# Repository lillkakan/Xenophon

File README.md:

# Xenophon split keyboard

Xenophon is a split keyboard with a design based on the ErgoDox EZ but for less keys for the thumps and another layout for the side keys.

## Features

### Ortholinear design

The keyboard features an ortholinear design based on the ErgoDox EZ.

### 70 buttons

The keyboard features 70 buttons to replicate a standard 60% keyboard as much as possible.
The Default layout is in swedish and has all the letters and numbers.

### TRS jack connection

The PCB is designed with a trs jack nicley placed between the tilted keys.
The two processors sent data through the serial bitbang protocol.

### Smart flashing design

I did not want to include a usb port on the right PCB i added two usb pins (D+ and D-) on both sides so that i could solder all the componens except the left processors and flash the right side easily.

### USB-C

The PCB features a usb type c port with capability to connect via a usb-c to usb-c cable or a standard usb-c to usb-a cable.

### 3D printable chassi

The chassi for the keyboard is 3D printable and is designed to be as small as possible while still protecting the PCB and the electrical components.

### Relativly low cost

The total cost of the key board is around 1 300 SEK.
Which is less than similar keyboards like the ErgoDox EZ.

## Made with

Quantum Mechanical Keyboard Firmware: [qmk_firmware](https://github.com/qmk/qmk_firmware)

## Made with help from

Keyboard layout editor: [keyboard-layout-editor.com](http://www.keyboard-layout-editor.com/)

Parametric Mechanical Keycap Library: [KeyV2](https://github.com/rsheldiii/KeyV2)

Keyboard Firmware Builder: [kbfirmware.com](https://kbfirmware.com/)

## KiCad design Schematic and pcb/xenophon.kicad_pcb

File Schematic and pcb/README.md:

# Xenophon Schematic and PCB

### Schematic

Feutures a usb-c connection on the left (master) side.

Because I wanted the right PCB to have as few IO connectors as possible i made the decision to place two pin holes connected to the USB pins on the processor.
This made is so I could connect the USB pins on the left side with the ones on the right side and flash the right processor with the USB-C cable before i soldered the left processor.
The two pins can also be connected to two resistors and soldered to a USB cable to flash to the processor directly.

Small reset buttons take up unneccesary space on the pcb i added pins for for both sides reset connection designed so that a regular cable could pull the reset down.

### Components

- 70x Cherry switches
- 70x Diodes
- 1x  USB-C Receptacle
- 2x  Atmega 32u4
- 2x  16 Mhz Crystal
- 2x  3.5 TRS jack
- 5x  0.1u  Capacitor
- 4x  18p   Capacitor
- 2x  1u    Capacitor
- 1x  4.7u  Capacitor
- 4x  10k   Ohm Resistors
- 2x  22    Ohm Resistors
- 2x  5.1k  Ohm Resistors

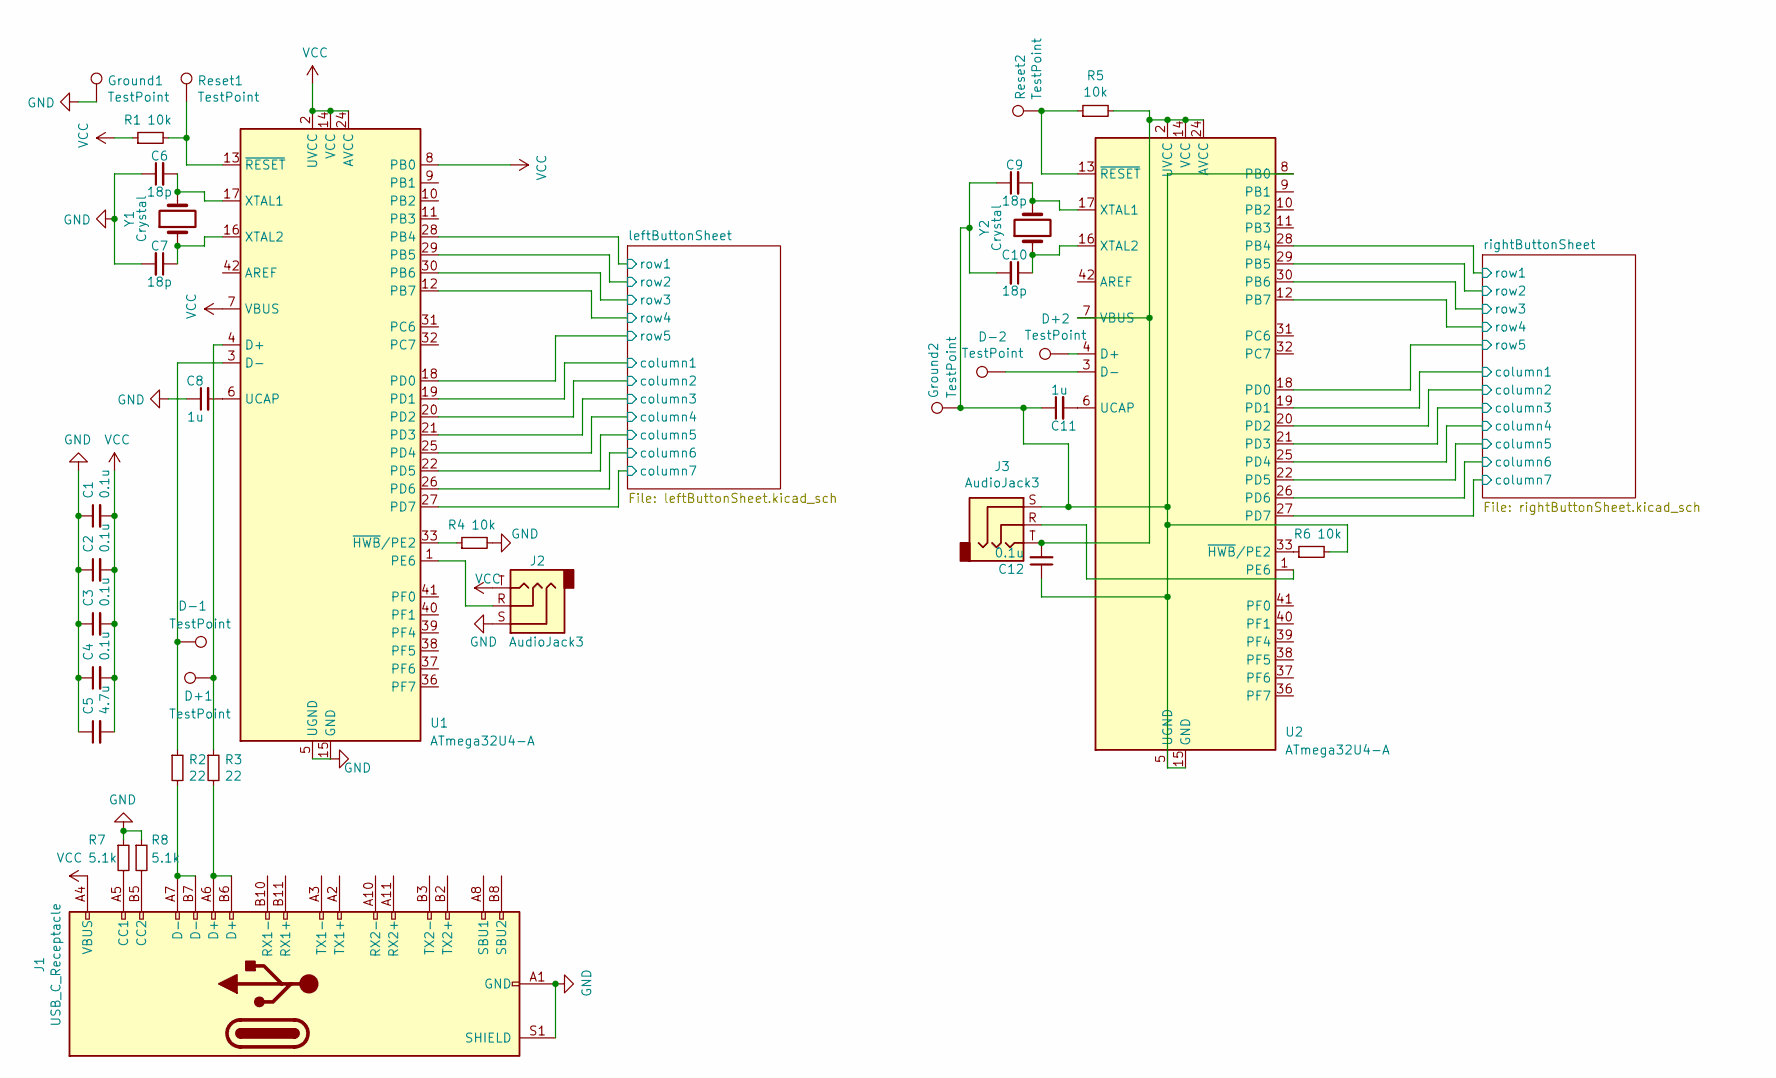
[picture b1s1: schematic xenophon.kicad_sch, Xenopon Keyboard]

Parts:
C1, C2, C3, C4, C12: 0.1u; C_1206_3216Metric
C5: 4.7u; C_1206_3216Metric
C6, C7, C9, C10: 18p; C_1206_3216Metric
C8, C11: 1u; C_1206_3216Metric
D+1, D+2: TestPoint; TestPoint_THTPad_2.0x2.0mm_Drill1.0mm
D-1, D-2: TestPoint; TestPoint_THTPad_2.0x2.0mm_Drill1.0mm
Ground1, Ground2: TestPoint; TestPoint_THTPad_2.0x2.0mm_Drill1.0mm
J1: USB_C_Receptacle; USB_C_Receptacle_HRO_TYPE-C-31-M-12
J2, J3: AudioJack3; Jack_3.5mm_Switronic_ST-005-G_horizontal
R1, R4, R5, R6: 10k; R_1206_3216Metric
R2, R3: 22; R_1206_3216Metric
R7, R8: 5.1k; R_1206_3216Metric
Reset1, Reset2: TestPoint; TestPoint_THTPad_2.0x2.0mm_Drill1.0mm
U1, U2: ATmega32U4-A; TQFP-44_10x10mm_P0.8mm
Y1, Y2: Crystal; Crystal_SMD_2016-4Pin_2.0x1.6mm

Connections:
/leftButtonSheet/column1: U1.19 (PD1); also elsewhere on the board
/leftButtonSheet/column2: U1.20 (PD2); also elsewhere on the board
/leftButtonSheet/column3: U1.21 (PD3); also elsewhere on the board
/leftButtonSheet/column4: U1.25 (PD4); also elsewhere on the board
/leftButtonSheet/column5: U1.22 (PD5); also elsewhere on the board
/leftButtonSheet/column6: U1.26 (PD6); also elsewhere on the board
/leftButtonSheet/column7: U1.27 (PD7); also elsewhere on the board
/leftButtonSheet/row1: U1.28 (PB4); also elsewhere on the board
/leftButtonSheet/row2: U1.29 (PB5); also elsewhere on the board
/leftButtonSheet/row3: U1.30 (PB6); also elsewhere on the board
/leftButtonSheet/row4: U1.12 (PB7); also elsewhere on the board
/leftButtonSheet/row5: U1.18 (PD0); also elsewhere on the board
/rightButtonSheet/column1: U2.19 (PD1); also elsewhere on the board
/rightButtonSheet/column2: U2.20 (PD2); also elsewhere on the board
/rightButtonSheet/column3: U2.21 (PD3); also elsewhere on the board
/rightButtonSheet/column4: U2.25 (PD4); also elsewhere on the board
/rightButtonSheet/column5: U2.22 (PD5); also elsewhere on the board
/rightButtonSheet/column6: U2.26 (PD6); also elsewhere on the board
/rightButtonSheet/column7: U2.27 (PD7); also elsewhere on the board
/rightButtonSheet/row1: U2.28 (PB4); also elsewhere on the board
/rightButtonSheet/row2: U2.29 (PB5); also elsewhere on the board
/rightButtonSheet/row3: U2.30 (PB6); also elsewhere on the board
/rightButtonSheet/row4: U2.12 (PB7); also elsewhere on the board
/rightButtonSheet/row5: U2.18 (PD0); also elsewhere on the board
unnamed: C7.1, U1.16 (XTAL2), Y1.1
unnamed: C8.2, U1.6 (UCAP)
unnamed: C10.1, U2.16 (XTAL2), Y2.1
unnamed: C11.2, U2.6 (UCAP)
unnamed: C12.2, J3.T, R5.2, U2.2 (UVCC), U2.7 (VBUS), U2.14 (VCC), U2.24 (AVCC), U2.34 (VCC), U2.44 (AVCC)
unnamed 99: D+1.1, R3.1, U1.4 (D+); also elsewhere on the board
unnamed 100: D+2.1, U2.4 (D+); also elsewhere on the board
unnamed 101: D-1.1, R2.1, U1.3 (D-); also elsewhere on the board
unnamed 102: D-2.1, U2.3 (D-); also elsewhere on the board
unnamed: J1.A5 (CC1), R7.2
unnamed: J1.A6 (D+), J1.B6 (D+), R3.2
unnamed: J1.A7 (D-), J1.B7 (D-), R2.2
unnamed: J1.B5 (CC2), R8.2
unnamed: J2.R, U1.1 (PE6)
unnamed: J3.R, U2.1 (PE6)
unnamed 111: R1.2, Reset1.1, U1.13 (~RESET); also elsewhere on the board
unnamed: R4.1, U1.33 (~HWB/PE2)
unnamed 113: R5.1, Reset2.1, U2.13 (~RESET); also elsewhere on the board
unnamed: R6.1, U2.33 (~HWB/PE2)
VCC: C1.2, C2.2, C3.2, C4.2, C5.2, J1.A4 (VBUS), J1.A9 (VBUS), J1.B4 (VBUS), J1.B9 (VBUS), J2.T, R1.1, U1.2 (UVCC), U1.7 (VBUS), U1.8 (PB0), U1.14 (VCC), U1.24 (AVCC), U1.34 (VCC), U1.44 (AVCC)

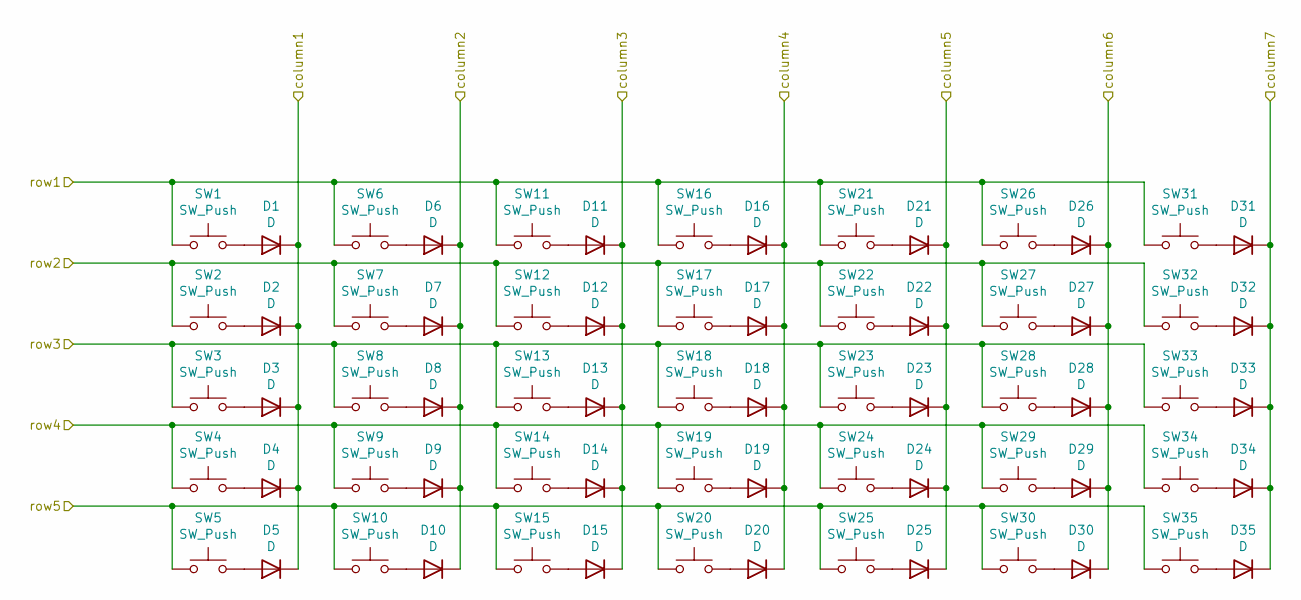
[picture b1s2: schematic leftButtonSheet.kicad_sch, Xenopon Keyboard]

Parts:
D1, D2, D3, D4, D5, D6, D7, D8, D9, D10, D11, D12, D13, D14, D15, D16, D17, D18, D19, D20, D21, D22, D23, D24, D25, D26, D27, D28, D29, D30, D31, D32, D33, D34, D35: D; D_1206_3216Metric
SW1, SW2, SW3, SW4, SW5: SW_Push; SW_Cherry_MX_1.50u_PCB
SW6, SW7, SW8, SW9, SW10, SW11, SW12, SW13, SW14, SW15, SW16, SW17, SW18, SW19, SW20, SW21, SW22, SW23, SW24, SW25, SW26, SW27, SW28, SW29, SW30, SW31, SW32, SW33, SW34, SW35: SW_Push; SW_Cherry_MX_1.00u_PCB

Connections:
/leftButtonSheet/column1: D1.1 (K), D2.1 (K), D3.1 (K), D4.1 (K), D5.1 (K); also elsewhere on the board
/leftButtonSheet/column2: D6.1 (K), D7.1 (K), D8.1 (K), D9.1 (K), D10.1 (K); also elsewhere on the board
/leftButtonSheet/column3: D11.1 (K), D12.1 (K), D13.1 (K), D14.1 (K), D15.1 (K); also elsewhere on the board
/leftButtonSheet/column4: D16.1 (K), D17.1 (K), D18.1 (K), D19.1 (K), D20.1 (K); also elsewhere on the board
/leftButtonSheet/column5: D21.1 (K), D22.1 (K), D23.1 (K), D24.1 (K), D25.1 (K); also elsewhere on the board
/leftButtonSheet/column6: D26.1 (K), D27.1 (K), D28.1 (K), D29.1 (K), D30.1 (K); also elsewhere on the board
/leftButtonSheet/column7: D31.1 (K), D32.1 (K), D33.1 (K), D34.1 (K), D35.1 (K); also elsewhere on the board
/leftButtonSheet/row1: SW1.1, SW6.1, SW11.1, SW16.1, SW21.1, SW26.1, SW31.1; also elsewhere on the board
/leftButtonSheet/row2: SW2.1, SW7.1, SW12.1, SW17.1, SW22.1, SW27.1, SW32.1; also elsewhere on the board
/leftButtonSheet/row3: SW3.1, SW8.1, SW13.1, SW18.1, SW23.1, SW28.1, SW33.1; also elsewhere on the board
/leftButtonSheet/row4: SW4.1, SW9.1, SW14.1, SW19.1, SW24.1, SW29.1, SW34.1; also elsewhere on the board
/leftButtonSheet/row5: SW5.1, SW10.1, SW15.1, SW20.1, SW25.1, SW30.1, SW35.1; also elsewhere on the board
unnamed: D1.2 (A), SW1.2
unnamed: D2.2 (A), SW2.2
unnamed: D3.2 (A), SW3.2
unnamed: D4.2 (A), SW4.2
unnamed: D5.2 (A), SW5.2
unnamed: D6.2 (A), SW6.2
unnamed: D7.2 (A), SW7.2
unnamed: D8.2 (A), SW8.2
unnamed: D9.2 (A), SW9.2
unnamed: D10.2 (A), SW10.2
unnamed: D11.2 (A), SW11.2
unnamed: D12.2 (A), SW12.2
unnamed: D13.2 (A), SW13.2
unnamed: D14.2 (A), SW14.2
unnamed: D15.2 (A), SW15.2
unnamed: D16.2 (A), SW16.2
unnamed: D17.2 (A), SW17.2
unnamed: D18.2 (A), SW18.2
unnamed: D19.2 (A), SW19.2
unnamed: D20.2 (A), SW20.2
unnamed: D21.2 (A), SW21.2
unnamed: D22.2 (A), SW22.2
unnamed: D23.2 (A), SW23.2
unnamed: D24.2 (A), SW24.2
unnamed: D25.2 (A), SW25.2
unnamed: D26.2 (A), SW26.2
unnamed: D27.2 (A), SW27.2
unnamed: D28.2 (A), SW28.2
unnamed: D29.2 (A), SW29.2
unnamed: D30.2 (A), SW30.2
unnamed: D31.2 (A), SW31.2
unnamed: D32.2 (A), SW32.2
unnamed: D33.2 (A), SW33.2
unnamed: D34.2 (A), SW34.2
unnamed: D35.2 (A), SW35.2

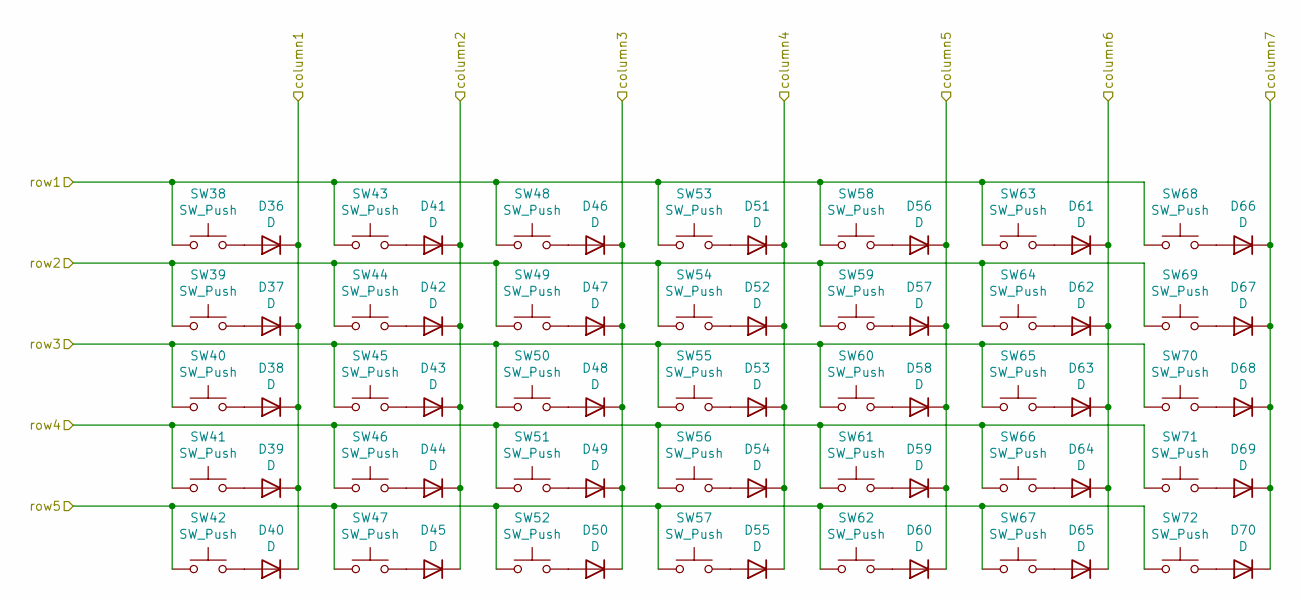
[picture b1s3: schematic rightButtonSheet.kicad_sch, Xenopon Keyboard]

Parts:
D36, D37, D38, D39, D40, D41, D42, D43, D44, D45, D46, D47, D48, D49, D50, D51, D52, D53, D54, D55, D56, D57, D58, D59, D60, D61, D62, D63, D64, D65, D66, D67, D68, D69, D70: D; D_1206_3216Metric
SW38, SW39, SW40, SW41, SW42, SW43, SW44, SW45, SW46, SW47, SW48, SW49, SW50, SW51, SW52, SW53, SW54, SW55, SW56, SW57, SW58, SW59, SW60, SW61, SW62, SW63, SW64, SW65, SW66, SW67: SW_Push; SW_Cherry_MX_1.00u_PCB
SW68, SW69, SW70, SW71, SW72: SW_Push; SW_Cherry_MX_1.50u_PCB

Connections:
/rightButtonSheet/column1: D36.1 (K), D37.1 (K), D38.1 (K), D39.1 (K), D40.1 (K); also elsewhere on the board
/rightButtonSheet/column2: D41.1 (K), D42.1 (K), D43.1 (K), D44.1 (K), D45.1 (K); also elsewhere on the board
/rightButtonSheet/column3: D46.1 (K), D47.1 (K), D48.1 (K), D49.1 (K), D50.1 (K); also elsewhere on the board
/rightButtonSheet/column4: D51.1 (K), D52.1 (K), D53.1 (K), D54.1 (K), D55.1 (K); also elsewhere on the board
/rightButtonSheet/column5: D56.1 (K), D57.1 (K), D58.1 (K), D59.1 (K), D60.1 (K); also elsewhere on the board
/rightButtonSheet/column6: D61.1 (K), D62.1 (K), D63.1 (K), D64.1 (K), D65.1 (K); also elsewhere on the board
/rightButtonSheet/column7: D66.1 (K), D67.1 (K), D68.1 (K), D69.1 (K), D70.1 (K); also elsewhere on the board
/rightButtonSheet/row1: SW38.1, SW43.1, SW48.1, SW53.1, SW58.1, SW63.1, SW68.1; also elsewhere on the board
/rightButtonSheet/row2: SW39.1, SW44.1, SW49.1, SW54.1, SW59.1, SW64.1, SW69.1; also elsewhere on the board
/rightButtonSheet/row3: SW40.1, SW45.1, SW50.1, SW55.1, SW60.1, SW65.1, SW70.1; also elsewhere on the board
/rightButtonSheet/row4: SW41.1, SW46.1, SW51.1, SW56.1, SW61.1, SW66.1, SW71.1; also elsewhere on the board
/rightButtonSheet/row5: SW42.1, SW47.1, SW52.1, SW57.1, SW62.1, SW67.1, SW72.1; also elsewhere on the board
unnamed: D36.2 (A), SW38.2
unnamed: D37.2 (A), SW39.2
unnamed: D38.2 (A), SW40.2
unnamed: D39.2 (A), SW41.2
unnamed: D40.2 (A), SW42.2
unnamed: D41.2 (A), SW43.2
unnamed: D42.2 (A), SW44.2
unnamed: D43.2 (A), SW45.2
unnamed: D44.2 (A), SW46.2
unnamed: D45.2 (A), SW47.2
unnamed: D46.2 (A), SW48.2
unnamed: D47.2 (A), SW49.2
unnamed: D48.2 (A), SW50.2
unnamed: D49.2 (A), SW51.2
unnamed: D50.2 (A), SW52.2
unnamed: D51.2 (A), SW53.2
unnamed: D52.2 (A), SW54.2
unnamed: D53.2 (A), SW55.2
unnamed: D54.2 (A), SW56.2
unnamed: D55.2 (A), SW57.2
unnamed: D56.2 (A), SW58.2
unnamed: D57.2 (A), SW59.2
unnamed: D58.2 (A), SW60.2
unnamed: D59.2 (A), SW61.2
unnamed: D60.2 (A), SW62.2
unnamed: D61.2 (A), SW63.2
unnamed: D62.2 (A), SW64.2
unnamed: D63.2 (A), SW65.2
unnamed: D64.2 (A), SW66.2
unnamed: D65.2 (A), SW67.2
unnamed: D66.2 (A), SW68.2
unnamed: D67.2 (A), SW69.2
unnamed: D68.2 (A), SW70.2
unnamed: D69.2 (A), SW71.2
unnamed: D70.2 (A), SW72.2

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
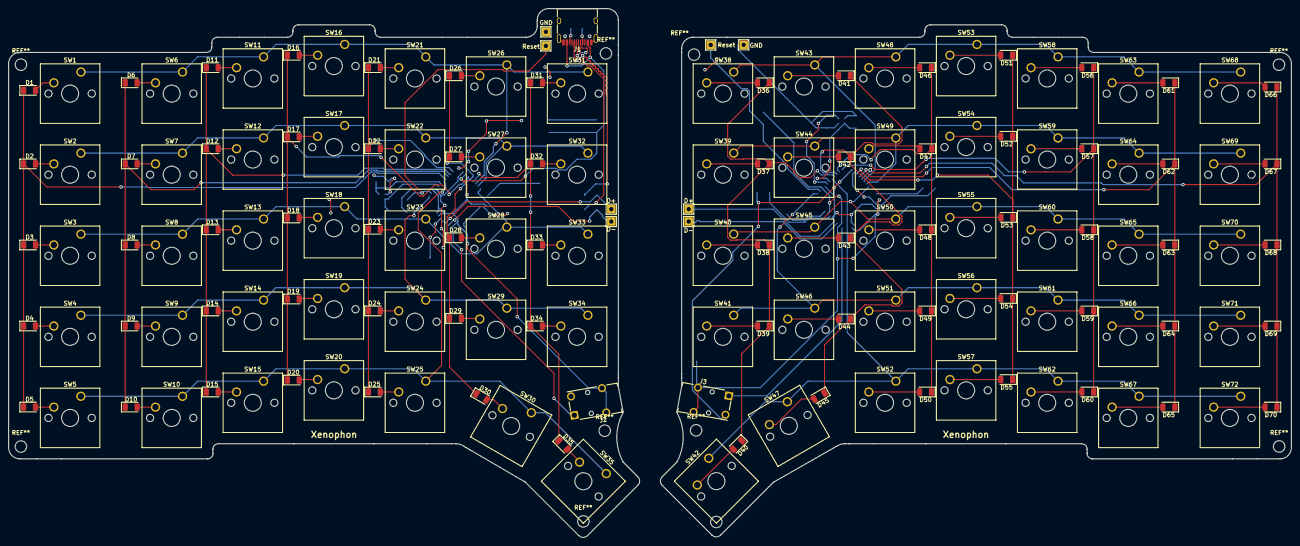
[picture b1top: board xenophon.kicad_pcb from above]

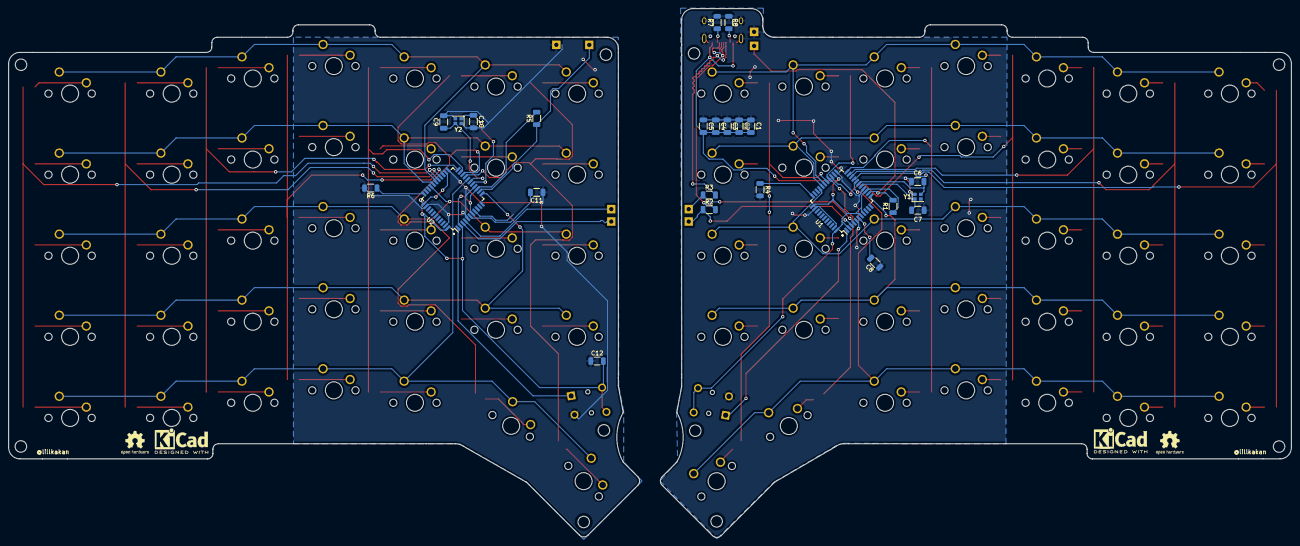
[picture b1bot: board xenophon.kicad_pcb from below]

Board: 2 copper layers, 301.4 x 124.2 mm, 175 parts (24 on the bottom side), 118 nets.

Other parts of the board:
D+: TestPoint; TestPoint_THTPad_2.0x2.0mm_Drill1.0mm
D+#2: TestPoint; TestPoint_THTPad_2.0x2.0mm_Drill1.0mm
D-: TestPoint; TestPoint_THTPad_2.0x2.0mm_Drill1.0mm
D-#2: TestPoint; TestPoint_THTPad_2.0x2.0mm_Drill1.0mm
GND: TestPoint; TestPoint_THTPad_2.0x2.0mm_Drill1.0mm
GND#2: TestPoint; TestPoint_THTPad_2.0x2.0mm_Drill1.0mm
Reset: TestPoint; TestPoint_THTPad_2.0x2.0mm_Drill1.0mm
Reset#2: TestPoint; TestPoint_THTPad_2.0x2.0mm_Drill1.0mm

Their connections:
unnamed 99: D+#2.1; also elsewhere on the board
unnamed 100: D+.1; also elsewhere on the board
unnamed 101: D-#2.1; also elsewhere on the board
unnamed 102: D-.1; also elsewhere on the board
unnamed 111: Reset.1; also elsewhere on the board
unnamed 113: Reset#2.1; also elsewhere on the board

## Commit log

2021-08-08 first
2021-08-27 main
2021-08-27 readmes
2021-08-27 tidy files
2021-09-02 New pcb design
2021-09-07 Updated chassi base and removed key file
2021-09-07 Changed name
2021-09-16 Wrote the intro readme.
2021-12-15 Removed debouncer and added a map for swedish layout.
2021-12-15 Added images and title block for the schematic.
2021-12-16 Removed shortcut and gerber file
2021-12-16 Removed unnecessary kicad files
2021-12-16 Corrected words and added components list.
2021-12-16 fixed list
2021-12-16 spelling
2021-12-24 Create LICENSE
2022-01-22 Updated the 3D models, made the chassi a bit smaller.
2022-01-22 Removed the backspace on the left side to make room for insert.
2022-01-22 Fixed the readme and added images.
2022-04-15 Added images
2022-04-15 Added 3d models to kicad footprints.
2022-04-15 Added swedish keymap.
2022-04-15 Started working on new pcb design without pre defined outline
2022-04-15 Added a library of printable keys.
2022-04-15 Updated chassi design
2022-04-15 Updated pcb and projekt files.
2022-04-24 Small changes to the chassi and their filenames
2022-04-24 Updated PCB files to the new verison of kicad.
2022-08-19 Updated firmware to work with new qmk version
